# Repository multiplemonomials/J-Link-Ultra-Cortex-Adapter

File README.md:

# J-Link Ultra Cortex Adapter

J-Links, as debug probes, are amazing.  They can talk to just about any processor, ARM or otherwise, in common use in the last decade.  The huge breadth of software and hardware compatibility available from one debug probe plus a set of adapters is incredible, and SEGGER deserves credit for getting this right.

Except... one thing.  The adapters they sell for connecting a J-Link to a 9-pin or 19-pin Cortex-Debug connector are just... bad.  They are bad, in fact, in several ways:
- They are expensive.  $40 for a tiny PCB with two connectors on it is too much.
- They don't connect the VCP (Virtual COM Port) pins.  Having a UART available to talk to the target device is a super useful feature of newer J-Links, but the design of these adapters just ignores it.  In fact, they don't even break the pins out, so they it's impossible to access without sketchy bodge wiring.
- The ribbon cable connectors have no keying, and the included ribbon cables don't either.  I have lost count of the number of times I've plugged in a debug cable backwards because there's nothing preventing one from doing so.
- Each $40 adapter only comes with one connector soldered: the 9-pin or the 19-pin.  Unless you have the knowledge to source and solder your own connector and cable, this means you need to buy two different adapters for working with 9 and 19-pin devices.

The Ultra Cortex Adapter in this repo tries to fix this badness in several ways.

First of all, this adapter uses proper keyed connectors for each of the ARM Cortex connections.  And these aren't just connectors with a little keying tab that can break off -- these are fully shrouded connectors that can take a beating and keep working.  

(note: the ARM standard says that the connections should be keyed via a missing pin 7 on the header and a filled pin 7 hole in the cable.  However, I've had a hard time sourcing this, so I've gone for the next best thing.  Plus, this way if you replace the cable the connector will still be keyed.)

Additionally, with this adapter, you get not one, not two, but *three* different connection options:
- Standard 9-pin Cortex Debug
- STMicro 14-pin STDC14
- Standard 19-pin Cortex Debug

Last but not least, the Ultra Cortex Adapter gives you access to all of the JTAG/SWD/VCP signals via convenient test points!  Because you never know when things are just going haywire and you need to be able to hook in a logic analyzer or oscilloscope, and it absolutely sucks to not have a convenient place to do that.

## ARM Debug Connector FAQ

- Q: Why are there so many GND lines on the connectors?
  - A: This is to create some level of electrical isolation between the JTAG lines by putting a GND conductor between each of the signal lines on the ribbon cable.
- Q: How do I protect JTAG/SWD pins on my board so that random electrical noise doesn't cause something to happen on the JTAG port of the MCU?
  - A: If your MCU has a TRST pin, one of the easiest ways to do this is to connect it to the debug connector and then pull the TRST pin to ground with a weak pulldown (10k?).  This ensures the JTAG TAP is held in reset at all times, except when a debugger is plugged in and brings TRST high.  However, TRST is not mapped on the standard ARM Cortex debug connectors.  SEGGER's adapters offer the option to convert the GNDDetect line into TRST, and that is supported by this adapter, but it might break compatibility with other standard-compliant debuggers.
  - If you don't have TRST, the [ARM recommended method](https://developer.arm.com/documentation/101416/0100/Hardware-Description/Target-Interfaces/Cortex-Debug-ETM) is to use 100kOhm resistors to pull up TMS and TDI to logic high and pull down TCLK to logic low.
- Q: What's the deal with the GNDDetect pin?
  - A: It's not documented well, but as far as I can understand, the idea of this pin is that it's pulled high on the board side and grounded on the debugger side.  This allows the board to know if a debugger is plugged in or not.  Unfortunately, SEGGER slightly disrupted this by leaving GNDDetect as NC by default, with a solder bridge option to connect it to TRST or GND.
- Q: How do we get Virtual COM Port on the 19-pin connector?
  - A: Unfortunately, even with 19 pins available, ARM didn't define a standard way to add UART to this connector.  Sadness.  And with SEGGER's default mapping (VCP_TX = TDI, VCP_RX = DBGREQ), the VCP_RX pin doesn't make it to *any* pin on the 19-pin connector.  To work around this, this adapter defines a custom mapping of VCP_RX to pin 7, the normally unused key pin on the connector.  This mapping is enabled by default, but can be disabled via cutting a jumper if you are using pin 7 for something else on your board.
- Q: How do I know if my J-Link supports Virtual COM Port?
  - A: This information is on the [SEGGER Wiki](https://wiki.segger.com/J-Link_Model_Overview), just click your J-Link model, find the Hardware Features table, and look for "VCOM".
- Q: How fast can the J-Link VCP port go?
  - A: Annoyingly, at the time of this writing, the J-Link serial port maxes out at 115200 baud on most J-Link probes.  Only the ULTRA V5 and ULTRA V6 support higher baudrates (up to 10Mbaud).  Here's hoping that SEGGER decides to get into the 21st century and add faster speeds on their standard models of debug probe...

## Choosing a Debug Connector for Your Board

With the large variety of debug connectors available, it can be difficult to determine the one you need for your application.  I've put together the below table to summarize which ones possess which features.

| Feature | 9-Pin Cortex Debug | 14-Pin STDC14 | 19-Pin Cortex Debug |
|---|---|---|---|
| JTAG | Yes | Yes | Yes |
| SWD | Yes | Yes | Yes |
| UART / Virtual COM Port | Only via nonstandard mapping. Not supported at the same time as JTAG. | Yes. Not supported at the same time as JTAG with J-Link. | Only via nonstandard mapping. Not supported at the same time as JTAG or with the J-Trace. |
| JTAG RTCK (return clock) | No | Yes | No |
| JTAG TRST | Only with SEGGER nonstandard mapping.  Requires changing a solder jumper on this adapter. | Only with SEGGER nonstandard mapping.  Requires changing a solder jumper on this adapter. | Only with SEGGER nonstandard mapping.  Requires changing a solder jumper on this adapter. |
| GNDDetect (ability for board to detect if a debugger is connected) | Yes (unless TRST is used) | Yes (unless TRST is used) | Yes (unless TRST is used) |
| Target Power | No | No | Yes |
| ETM (Embedded Trace Macrocell) | No | No | Yes |

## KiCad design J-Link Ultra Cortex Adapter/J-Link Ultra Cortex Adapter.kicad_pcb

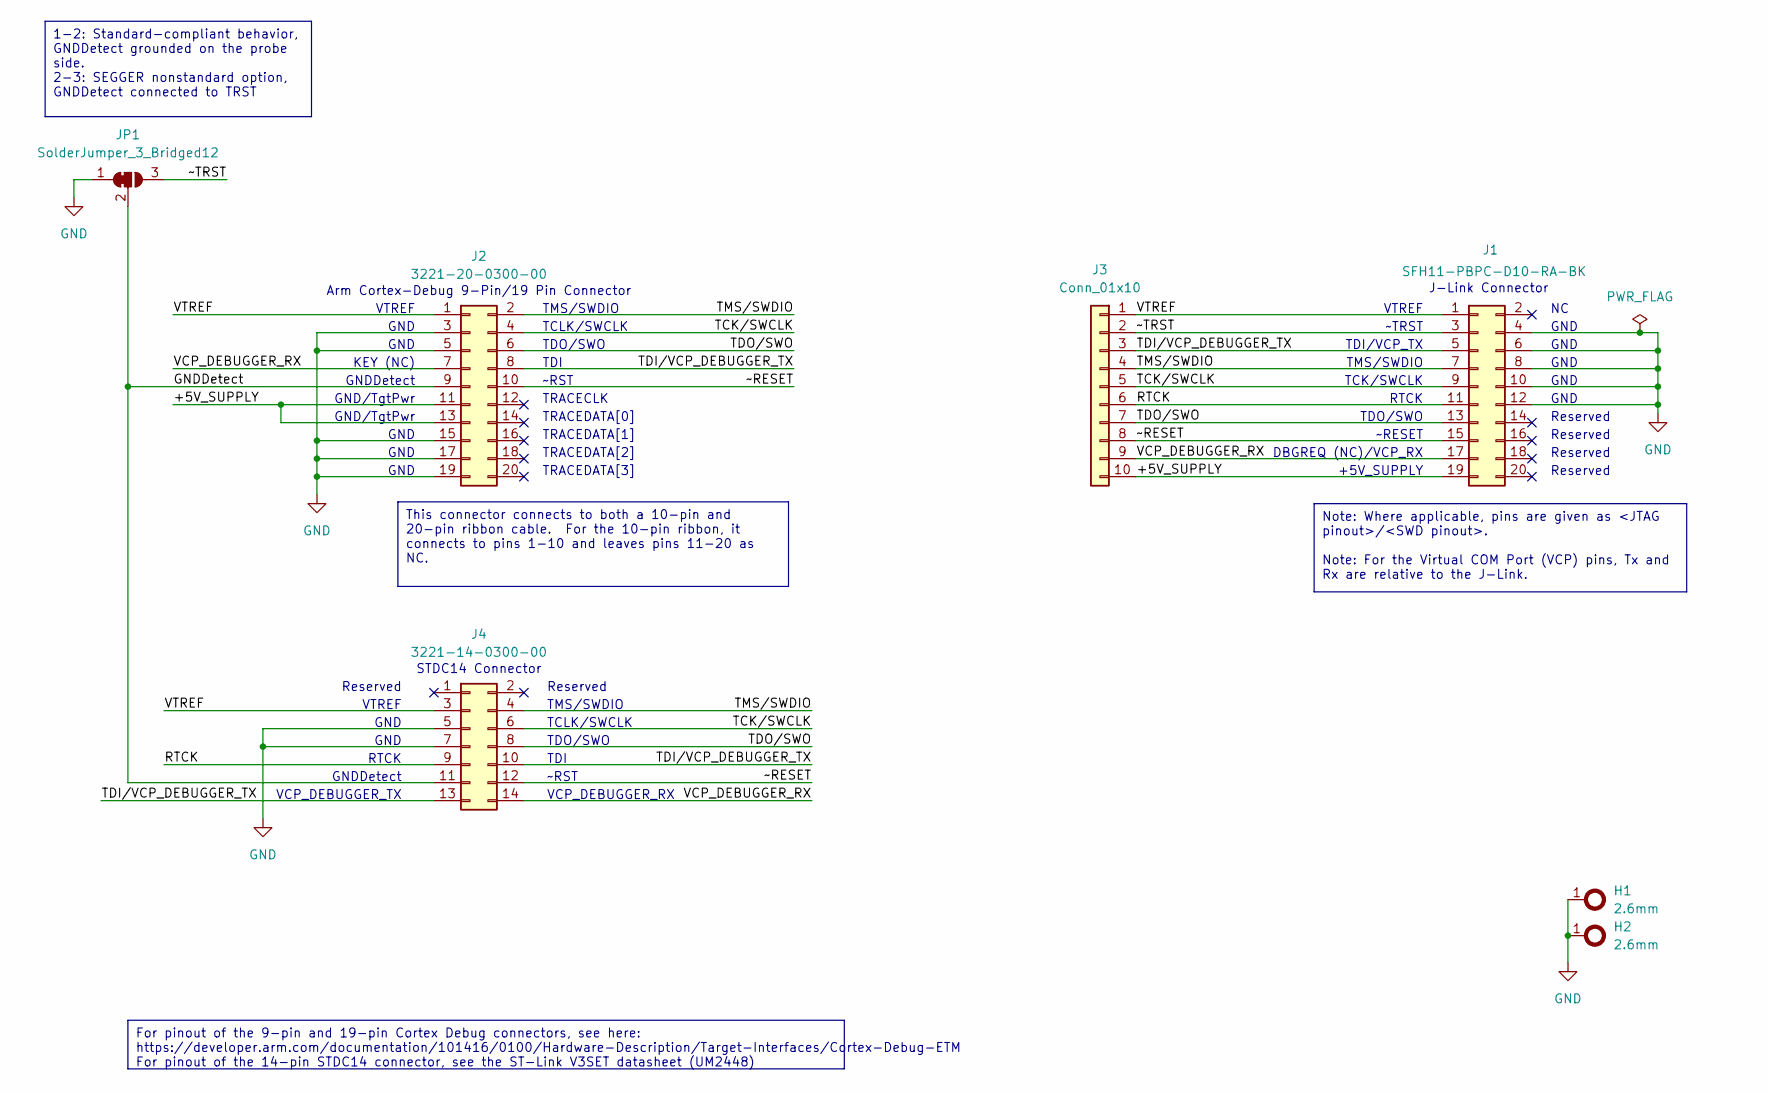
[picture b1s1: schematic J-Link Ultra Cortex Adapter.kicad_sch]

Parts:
H1, H2: 2.6mm; StencilAlignmentHole
J1: SFH11-PBPC-D10-RA-BK
J2: 3221-20-0300-00
J3: Conn_01x10; PinHeader_1x10_P2.54mm_Vertical
J4: 3221-14-0300-00
JP1: SolderJumper_3_Bridged12; SolderJumper-3_P1.3mm_Bridged2Bar12_Pad1.0x1.5mm_NumberLabe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

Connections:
/+5V_SUPPLY: J1.19, J2.11, J2.13, J3.10
/GNDDetect: J2.9, J4.11, JP1.2 (C)
/RTCK: J1.11, J3.6, J4.9
/TCK/SWCLK: J1.9, J2.4, J3.5, J4.6
/TDI/VCP_DEBUGGER_TX: J1.5, J2.8, J3.3, J4.10, J4.13
/TDO/SWO: J1.13, J2.6, J3.7, J4.8
/TMS/SWDIO: J1.7, J2.2, J3.4, J4.4
/VCP_DEBUGGER_RX: J1.17, J2.7, J3.9, J4.14
/VTREF: J1.1, J2.1, J3.1, J4.3
/~RESET: J1.15, J2.10, J3.8, J4.12
/~TRST: J1.3, J3.2, JP1.3 (B)
GND: H1.1, H2.1, J1.4, J1.6, J1.8, J1.10, J1.12, J2.3, J2.5, J2.15, J2.17, J2.19, J4.5, J4.7, JP1.1 (A)

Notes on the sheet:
1-2: Standard-compliant behavior, GNDDetect grounded on the probe side. 2-3: SEGGER nonstandard option, GNDDetect connected to TRST
This connector connects to both a 10-pin and 20-pin ribbon cable. For the 10-pin ribbon, it connects to pins 1-10 and leaves pins 11-20 as NC.
Note: Where applicable, pins are given as <JTAG pinout>/<SWD pinout>. Note: For the Virtual COM Port (VCP) pins, Tx and Rx are relative to the J-Link.
For pinout of the 9-pin and 19-pin Cortex Debug connectors, see here: https://developer.arm.com/documentation/101416/0100/Hardware-Description/Target-Interfaces/Cortex-Debug-ETM For pinout of the 14-pin STDC14 connector, see the ST-Link V3SET datasheet (UM2448)
Arm Cortex-Debug 9-Pin/19 Pin Connector
GND/TgtPwr
VCP_DEBUGGER_RX
TCK/SWCLK
TDO/SWO
~TRST
RTCK
GNDDetect
TCLK/SWCLK
GND
KEY (NC)
~RST
VTREF
Reserved
~RESET
J-Link Connector
VCP_DEBUGGER_TX
TRACECLK
TRACEDATA[2]
+5V_SUPPLY
TDI
TRACEDATA[3]
STDC14 Connector
TRACEDATA[0]
TRACEDATA[1]
TMS/SWDIO
TDI/VCP_TX
DBGREQ (NC)/VCP_RX

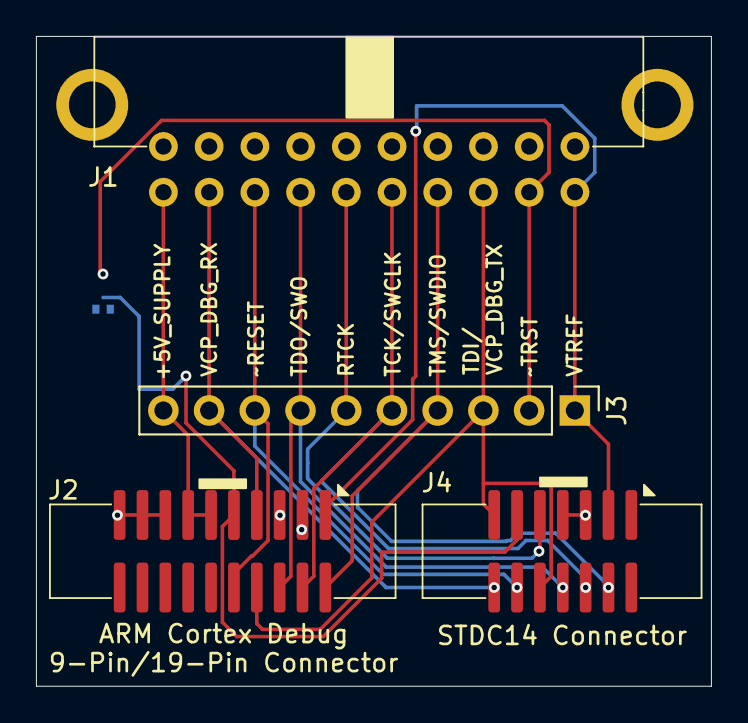
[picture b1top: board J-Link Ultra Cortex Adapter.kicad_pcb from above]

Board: 2 copper layers, 37.5 x 36.1 mm, 7 parts (1 on the bottom side), 12 nets.

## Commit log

2024-07-27 Initial commit, basic PCB done
2024-07-27 Add kibot files
2024-07-27 Try and fix quoting
2024-07-28 Fix some deprecated Kibot stuff. Can't easily fix some of the warnings though, oh well...
2024-07-28 Add PCBWay design rules
2024-11-01 Add baud rate info
2024-11-01 Add stencil alignment holes
2024-11-01 Remove remap:
